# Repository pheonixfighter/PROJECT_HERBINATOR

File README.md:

<!--
  GitHub project README for Project Herbinator.
  Drop this in the repo root as README.md.
-->

<div align="center">

# Project Herbinator 🌱

### Landon Wardle, Robert Cromer, Jasmine Sellers, Juan Ramirez, Zach Worcester, Hunter Mass
### May, 2026

A low-cost smart watering device that keeps small plants alive on its own.
An ESP32-S3 runs a finite-state machine that samples soil moisture, factors in
temperature and humidity, and pumps water only when the plant actually needs it.
A companion Python app monitors the device over Wi-Fi.

<!-- Badge row — these render as little pills on GitHub -->

</div>

---

## Table of Contents

1. [Overview](#overview)
2. [How It Works](#how-it-works)
3. [Hardware](#hardware)
4. [Pinout](#pinout)
5. [Firmware](#firmware)
6. [Calibration](#calibration)
7. [HTTP API](#http-api)
8. [Python Application](#python-application)
9. [Configuration](#configuration)
10. [State and LED Reference](#state-and-led-reference)
11. [Data Logging](#data-logging)
12. [Known Limitations](#known-limitations)

---

# Overview

Herbinator is an automated irrigation device for small-scale plants such as indoor gardens or
windowsill collections. It continuously monitors soil moisture and waters the plant only when the
soil dries below a calibrated threshold, then stops once the soil is satisfied. The goal is to cut
out manual watering while using water efficiently.

The brain is an **ESP32-S3** running firmware structured as a finite-state machine (FSM). The
board reads a capacitive moisture sensor and a DHT11 temperature/humidity sensor, drives a small
submersible pump, and protects itself with a float switch that prevents the pump from running dry.
All readings and pump events are logged to an SD card, and the device hosts a small HTTP server so
a Python app can monitor it remotely.

> [!NOTE]
> To see the Herbinator Roadmap and Project Specification Template
> see the Documentation folder in the repository.

# How It Works

At a high level, Herbinator spends most of its life idling and sampling the moisture sensor
occasionally. When the soil gets too dry it starts the pump, and once the soil is wet enough (or a
safety limit trips) it stops and goes back to idling.

| Step | What happens |
|:-----|:-------------|
| Idle / monitor | The FSM sits in `WaterLoop`, sampling the moisture sensor at a slow interval to save power. |
| Decide | If moisture drops to or below the *on* threshold, it enters `PumpOn`. The threshold is nudged by the current temperature and humidity (see VPD below). |
| Water | The pump runs until soil moisture rises past the *off* threshold, the reservoir runs dry, or a maximum run-time is reached. |
| Recover | After watering it returns to monitoring. If the pump ran for the full safety limit, it first cools down in `PumpCD`. |
| Protect | If the float switch reports no water, or a sensor stops responding, the FSM jumps to the matching error state and parks the pump. |

> [!NOTE]
> The decision threshold is adjusted using **Vapor Pressure Deficit (VPD)**, which is a measure of how fast
> a plant loses water to the air. Hotter, drier air raises the threshold so the plant is watered a
> little sooner; cool, humid air lowers it so watering is delayed. The base *on* threshold is 25%
> and the *off* threshold is 75%, with VPD shifting the *on* threshold by up to +-10%.

# Hardware

Core components for the v1.0 custom PCB:

| Component | Part | Purpose |
|:----------|:-----|:--------|
| Microcontroller | ESP32-S3-WROOM-1 | Runs the FSM firmware, all I/O, and Wi-Fi for Python App |
| Moisture Sensor | Capacitive soil moisture sensor | Estimates soil moisture |
| Temp/Humidity Sensor | DHT11 (U5) | Measures temperature (°C) and humidity |
| Water Pump | 5 V DC mini submersible pump | Delivers water to the plant |
| Float Switch | Magnetic float switch (J5) | Measures if water is available to pump |
| SD Card Reader | SPI SD card module (J4) | Logs readings and pump events to a `.csv` file |
| State LEDs | Green (D2), Blue (D3), Red (D4) | Visual feedback |
| Calibration Button | SW3 tactile push-button | Triggers the moisture calibration routine |
| 3.3 V regulator | AP2112K-3.3V | Powers the ESP32-S3 and sensor logic |
| 5 V regulator + jack | AMS1117-5.0 + 5.5 mm barrel jack | Powers the pump from a wall adapter |
| USB-C | USB-C receptacle (J1, FUSB302) | Alternate power input and serial programming |

> [!NOTE]
> There is no circuitry to switch from the USB-C Port to the
> barrel jack because the PCB was created to have two
> distinct power rails. Both must be plugged in for
> correct results.

> [!NOTE]
> The PCB is still being assembled. More documentation
> and photos will be available once it is done.

# Pinout

GPIO assignments as defined at the top of `ESPMain.ino`:

| Function | Pin | Function | Pin |
|:---------|:---:|:---------|:---:|
| Pump (servo/ESC signal) | 7 | Green LED | 13 |
| Float switch drive (high) | 0 | Blue LED | 12 |
| Float switch read | 10 | Red LED | 11 |
| Moisture sensor (analog) | 4 | Calibration button | 6 |
| DHT11 data | 5 | SD `SCK` | 3 |
| SD `CS` | 18 | SD `MISO` | 46 |
| SD `MOSI` | 8 | | |

> [!NOTE]
> The pump is driven through the `ESP32Servo` library as an ESC-style PWM signal, **not** a raw
> on/off pin. A write of `0` runs the pump at full speed and `90` stops it completely.

# Firmware

The firmware lives in `main/ESPMain/ESPMain.ino` and is built and flashed with the **Arduino IDE** targeting an **ESP32-S3**.

### Required libraries

Install these through the Arduino Library Manager:

`DHT11` · `ESP32Servo` (provides `ESP32PWM`) · `ArduinoJson`

Remaining libraries are available on the **ESP32-S3** by default.

### Build & flash

1. Install the **ESP32 board package** in the Arduino IDE.
2. Open `main/ESPMain/ESPMain.ino`.
3. Select an **ESP32-S3** board and the correct serial port.
4. Set your Wi-Fi credentials (see [Configuration](#configuration)).
5. Upload, then open the Serial Monitor at **9600 baud** (or change the baud rate specified in the code) to watch state transitions.

> [!WARNING]
> On boot the firmware **blocks until the SD card initializes**. If no card is inserted, the red
> LED stays on and the device prints an SD warning in a loop instead of starting the FSM.

# Calibration

Capacitive moisture sensors read different raw values per unit and per soil type, so Herbinator
calibrates against your specific sensor and soil. Calibration values are saved to a simulated
**EEPROM** on the **ESP32-S3** so they are non-volatile.

To calibrate, **hold the button (SW3) for 2 seconds** from the idle state. Herbinator then uses
the LEDs to guide you:

| Step | LED cue | What to do |
|:-----|:--------|:-----------|
| Start | Red flashes 3s | Calibration mode has begun |
| Dry point | Green flashes | Place the sensor in dry soil / air, then press and hold the button |
| Wet point | Blue flashes | For best results water your plant, then place the sensor in the expected wet soil, then press and hold the button. Partially submerging the sensor in a cup of water is also acceptable. |
| Done | All LEDs blink | Done! Wait for Herbinator to resume the water loop. |

> [!NOTE]
> If the stored calibration is missing or invalid on startup, the device automatically drops into
> the calibration routine rather than watering with bad thresholds.

# HTTP API

After connecting to Wi-Fi the device registers an mDNS name and serves a small HTTP API on **port
80**. With mDNS working it is reachable at `http://herbnet.local/`, or directly by its IP address.

| Method | Endpoint | Returns |
|:------:|:---------|:--------|
| `GET` | `/` | JSON snapshot: `temperature`, `humidity`, `moisture`, `state`, `time` |
| `GET` | `/time` | Current time string (synced over NTP) |
| `GET` | `/temperature` | Last temperature reading |
| `GET` | `/humidity` | Last humidity reading |
| `GET` | `/moisture` | Last moisture percentage |
| `GET` | `/state` | Current FSM state name |
| `POST` | `/water` | Acknowledges a manual-water request |

<details>
<summary><b>Example <code>/</code> response</b></summary>

<br>

```json
{
  "temperature": 67,
  "humidity": 21,
  "moisture": 69,
  "state": "PumpOn",
  "time": "2026-05-28 13:45:27"
}
```

</details>

> [!NOTE]
> The `/water` endpoint currently returns a `watering` status but does not yet trigger the pump —
> the actual watering hook is still a TODO. The `/pause` and `/resume` endpoints are scaffolded in
> the firmware but commented out, so the app's pause/resume buttons have nothing to talk to yet.

# Python Application

The desktop app in `python/herbinator.py` is a **Tkinter** GUI that polls the device and displays
live data. It records each sensor's value plus the device's current state, and pulls the timestamp
from the device (synced over NTP).

### Running it

```bash
pip install requests
python herbinator.py
```

### What it shows

The window displays **Temperature**, **Humidity**, **Moisture**, **State**, and **Last Update**,
plus a scrolling log of every request and response. It refreshes automatically every **30 seconds**.

### Buttons

| Button | Action |
|:-------|:-------|
| Water Plant | Sends `POST /water` |
| Pause | Sends `POST /pause` |
| Pause 1 Minute | Sends `POST /pause` with a 60-second duration |
| Resume | Sends `POST /resume` |

> [!NOTE]
> Set `BASE_URL` at the top of `herbinator.py` to your device's address — either `http://herbnet.local`
> (if mDNS resolves on your network) or the device's IP shown in the Serial Monitor on boot. If the
> device is unreachable, every field shows `Disconnected` and the error appears in the log box.

# Configuration

Most tunable values are constants near the top of `ESPMain.ino`:

| Setting | Constant | Default |
|:--------|:---------|:--------|
| Wi-Fi SSID | `ROUTER_NAME` | `HerbyIOT` |
| Wi-Fi password | `ROUTER_PASSWORD` | `herbinator` |
| mDNS name | `mdnsName` | `herbnet` → `herbnet.local` |
| Timezone offset | `gmtOffset_sec` | `-28800` (PST) |
| Moisture *on* threshold | `ON_THRESHOLD_BASE` | `0.25` |
| Moisture *off* threshold | `OFF_THRESHOLD_BASE` | `0.75` |
| Max pump run-time | `MAX_PUMP_ON_MS` | 45s |
| Long-run pump cooldown | `PUMP_CD_MILLIS` | 5 min |
| Idle sample interval | `WATER_LOOP_SAMPLE_MS` | 5s |
| Calibration hold time | `CALIBRATION_HOLD_MS` | 2s |

> [!WARNING]
> Wi-Fi credentials are stored in plain text in the source. Don't commit real network credentials
> to a public repository.

# State and LED Reference

The FSM has the following states. The three status LEDs signal what the device is doing at a glance:

| State | Meaning | LEDs |
|:------|:--------|:-----|
| `MainLoop` | Validates calibration, checks for water, then enters monitoring | Green |
| `WaterLoop` | Idle monitoring; sampling soil moisture | Green |
| `PumpOn` | Pump running | Blue |
| `PumpOff` | Pump shutting off | Off |
| `PumpCD` | Cooldown after a long pump run | Red (flashing) |
| `NoWater` | Reservoir empty (float switch) — pump parked | Red + Blue |
| `RedFlash` | Entry into calibration | Red (flashing) |
| `PromptDry` | Waiting for dry calibration point | Green (flashing) |
| `PromptWet` | Waiting for wet calibration point | Blue (flashing) |
| `ButtonPressed` / `CalibrationButtonYield` | Hold-detection during calibration | N/A |
| `CalibrationDone` | Calibration saved | All (blinking) |
| `MoistureSensorFail` | Moisture sensor out of range / unresponsive | Red (fast flash) + Blue |
| `TempSensorFail` | DHT11 unresponsive | Red (fast flash) + Green |

# Data Logging

When an SD card is present, the firmware appends every sensor cycle and pump event to
`/herbinator_logs.txt` as CSV, flushing to the card every 30 seconds. Columns:

```text
timestamp_ms, state, rawMoist, moist_pct, on_thresh, temp_c,
humidity_pct, vpd_kpa, dht_ok, pump_on, water_raw, water_present
```

This makes it easy to pull the card afterward and analyze how the soil dried and recovered around
each watering event. It is recommended to do this in MATLAB or similar software that can crunch 
large .csv files quickly.

# Known Limitations

- **Manual watering isn't wired up.** `/water` returns a status but doesn't actually run the pump yet.
- **Pause/resume are stubs.** Those firmware endpoints are commented out, so the app's Pause / Resume / Pause 1 Minute buttons have no effect on the device.
- **CLI is a placeholder.** `python/interface.py` is an early scaffold and not yet a working interface.
- **Credentials are hardcoded.** Wi-Fi SSID/password live in the firmware source.

<!--
  Suggested next steps for the team:
  - Implement the watering hook behind /water and reinstate /pause + /resume to match the app.
  - Move Wi-Fi credentials out of source (e.g. a config the user enters, or a secrets header that's gitignored).
  - Finish interface.py or remove it if the Tkinter app is the path forward.
  - Consider documenting the BOM footprint lessons from the spec doc here too.
-->

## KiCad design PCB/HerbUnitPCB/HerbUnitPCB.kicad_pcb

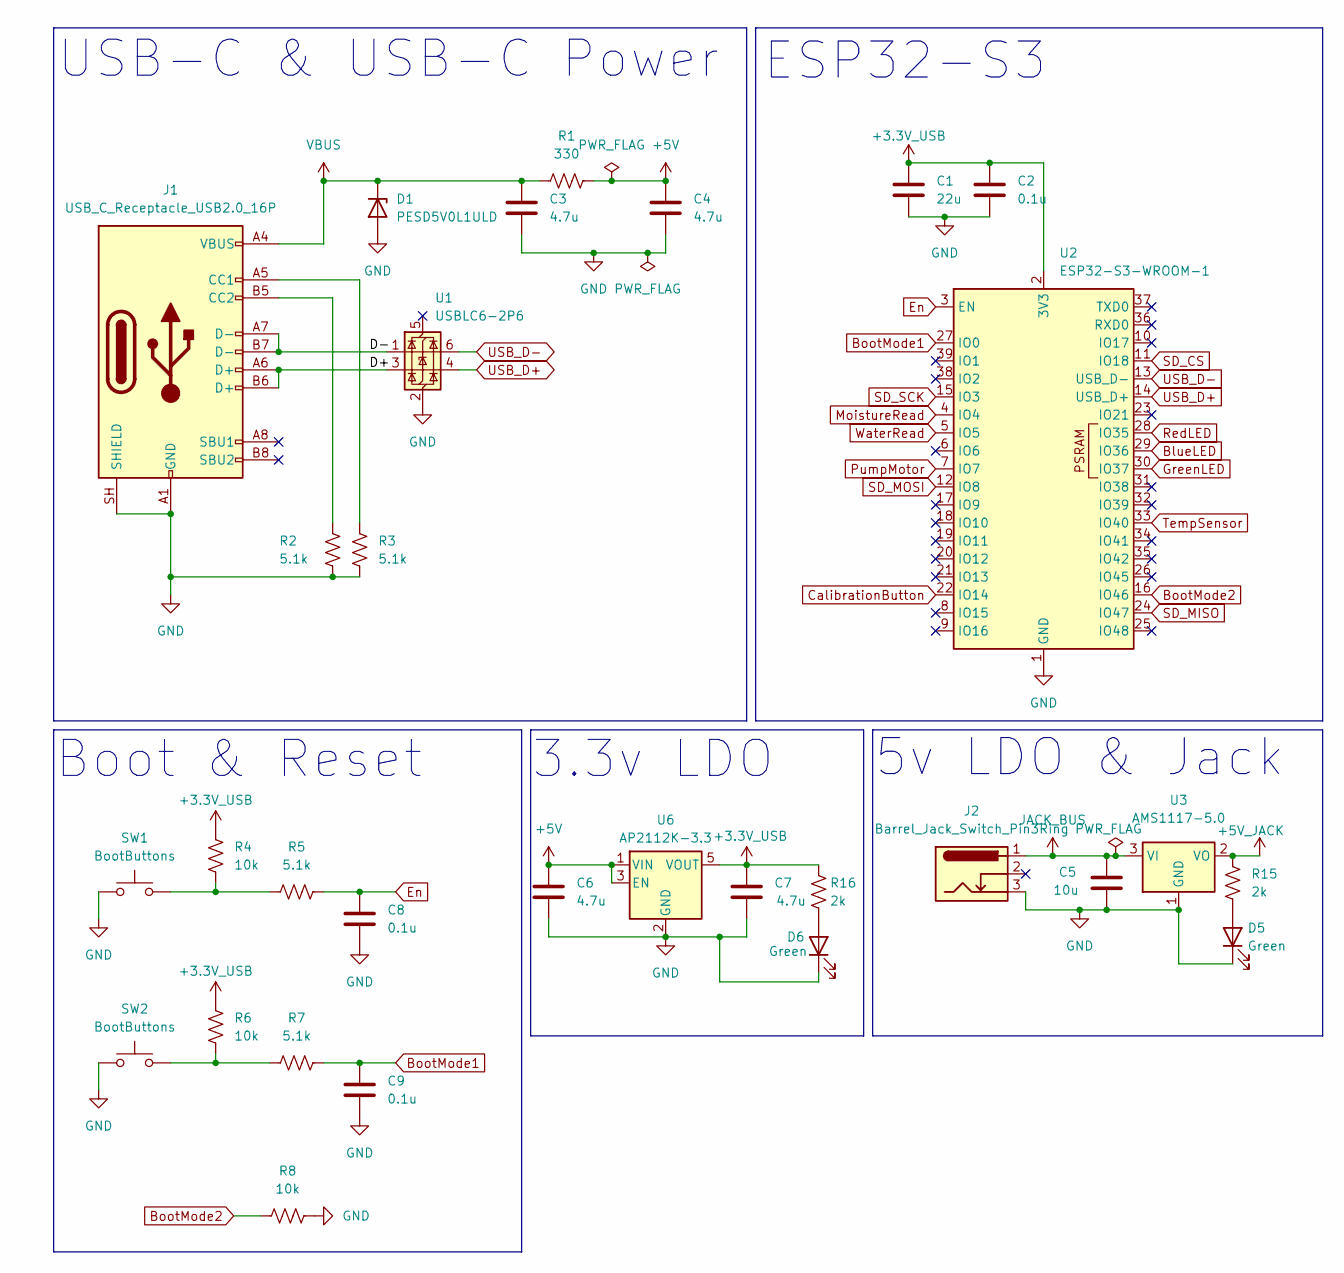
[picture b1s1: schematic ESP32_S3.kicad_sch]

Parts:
C1: 22u; C_0805_2012Metric; MPN GRM21BR61E226ME44K
C2, C8, C9: 0.1u; C_0402_1005Metric; MPN GRM155R62A104KE14D
C3, C4, C6, C7: 4.7u; C_0402_1005Metric; MPN GRM155R61A475MEAAD
C5: 10u; C_1206_3216Metric; MPN GRM319R61E106KA12D
D1: PESD5V0L1ULD; D_SOD-882D; MPN SOD882
D5, D6: Green; LED_APT2012CGCK
J1: USB_C_Receptacle_USB2.0_16P; USB_C_Receptacle_G-Switch_GT-USB-7010ASV; MPN UJ31-CH-3-SMT-TR
J2: Barrel_Jack_Switch_Pin3Ring; BarrelJack_Horizontal; MPN PJ-002A
R1: 330; R_0805_2012Metric; MPN RC0805FR-10330RL
R2, R3, R5, R7: 5.1k; R_0402_1005Metric; MPN RT0402DRE075K1L
R4, R6, R8: 10k; R_0402_1005Metric; MPN RC0402FR-1310KL
R15, R16: 2k; R_0402_1005Metric; MPN AC0402FR-072KL
SW1, SW2: BootButtons; SW_SPST_B3U-1000P; MPN B3U-1000P
U1: USBLC6-2P6; SOT-666; MPN USBLC6-2P6
U2: ESP32-S3-WROOM-1; MPN ESP32-S3-WROOM-1-N8
U3: AMS1117-5.0; SOT-223-3_TabPin2; MPN AMS1117-5.0(XBLW)
U6: AP2112K-3.3; SOT-23-5; MPN AP2112K-3.3TRG1

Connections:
+3.3V_USB: C1.1, C2.1, C7.1, R4.1, R6.1, R16.1, U2.2 (3V3), U6.5 (VOUT); also elsewhere on the board
+5V: C4.1, C6.1, R1.2, U6.1 (VIN), U6.3 (EN)
+5V_JACK: R15.1, U3.2 (VO); also elsewhere on the board
/ESP32-S3/D+: J1.A6 (D+), J1.B6 (D+), U1.3 (I/O2)
/ESP32-S3/D-: J1.A7 (D-), J1.B7 (D-), U1.1 (I/O1)
BlueLED: U2.29 (IO36); also elsewhere on the board
BootMode1: C9.1, R7.2, U2.27 (IO0)
BootMode2: R8.1, U2.16 (IO46)
CalibrationButton: U2.22 (IO14); also elsewhere on the board
En: C8.1, R5.2, U2.3 (EN)
GND: C1.2, C2.2, C3.2, C4.2, C5.2, C6.2, C7.2, C8.2, C9.2, D1.2 (A), D5.1 (K), D6.1 (K), J1.A1 (GND), J1.A12 (GND), J1.B1 (GND), J1.B12 (GND), J1.SH (SHIELD), J2.3, R2.1, R3.2, R8.2, SW1.1, SW2.1, U1.2 (GND), U2.1 (GND), U2.40 (GND), U2.41 (GND), U3.1 (GND), U6.2 (GND); also elsewhere on the board
GreenLED: U2.30 (IO37); also elsewhere on the board
JACK_BUS: C5.1, J2.1, U3.3 (VI)
MoistureRead: U2.4 (IO4); also elsewhere on the board
unnamed: D5.2 (A), R15.2
unnamed: D6.2 (A), R16.2
unnamed: J1.A5 (CC1), R3.1
unnamed: J1.B5 (CC2), R2.2
unnamed: R4.2, R5.1, SW1.2
unnamed: R6.2, R7.1, SW2.2
PumpMotor: U2.7 (IO7); also elsewhere on the board
RedLED: U2.28 (IO35); also elsewhere on the board
SD_CS: U2.11 (IO18); also elsewhere on the board
SD_MISO: U2.24 (IO47); also elsewhere on the board
SD_MOSI: U2.12 (IO8); also elsewhere on the board
SD_SCK: U2.15 (IO3); also elsewhere on the board
TempSensor: U2.33 (IO40); also elsewhere on the board
USB_D+: U1.4 (I/O2), U2.14 (USB_D+)
USB_D-: U1.6 (I/O1), U2.13 (USB_D-)
VBUS: C3.1, D1.1 (K), J1.A4 (VBUS), J1.A9 (VBUS), J1.B4 (VBUS), J1.B9 (VBUS), R1.1
WaterRead: U2.5 (IO5); also elsewhere on the board

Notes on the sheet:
ESP32-S3
5v LDO & Jack
3.3v LDO
Boot & Reset
USB-C & USB-C Power

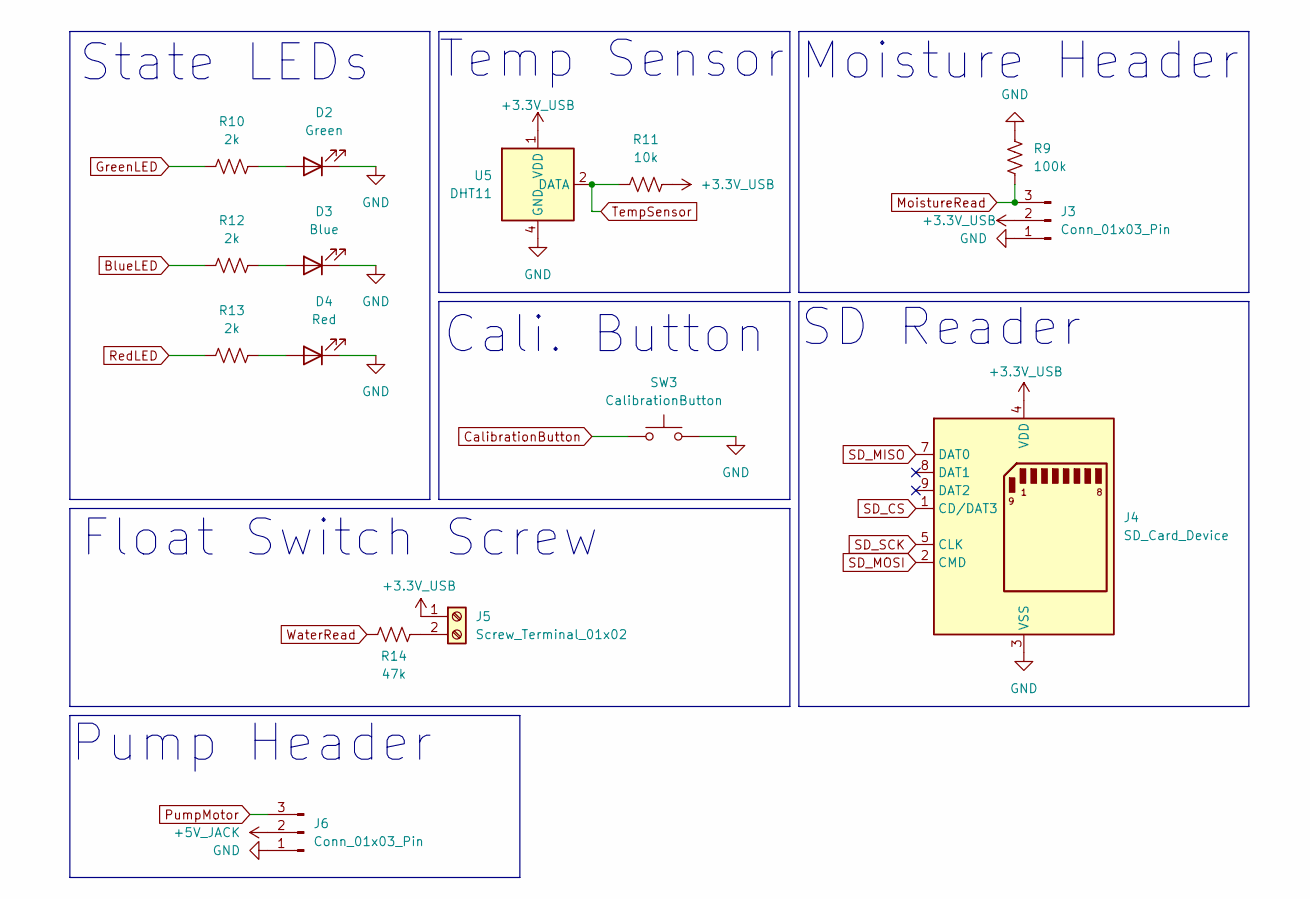
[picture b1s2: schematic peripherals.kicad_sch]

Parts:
D2: Green; LED_APT2012CGCK; MPN APT2012CGCK
D3: Blue; LED_APT2012VBC_D; MPN APT2012VBC_D
D4: Red; LED_APT2012EC; MPN APT2012EC
J3, J6: Conn_01x03_Pin; PinHeader_1x03_P2.54mm_Horizontal; MPN 61300311021
J4: SD_Card_Device; SD_Hirose_DM1AA_SF_PEJ82; MPN MSD-3-A
J5: Screw_Terminal_01x02; TerminalBlock_Phoenix_MKDS-1,5-2-5.08_1x02_P5.08mm_Horizont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; MPN 1715721
R9: 100k; R_0805_2012Metric; MPN RC0805JR-07100KL
R10, R12, R13: 2k; R_0402_1005Metric; MPN AC0402FR-072KL
R11: 10k; R_0402_1005Metric; MPN RC0402FR-1310KL
R14: 47k; R_0805_2012Metric; MPN RT0805FRE0747KL
SW3: CalibrationButton; SW_Push_1P1T_NO_CK_PTS125Sx43SMTR; MPN PTS125SM43
U5: DHT11; Aosong_DHT11_5.5x12.0_P2.54mm; MPN DHT11

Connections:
+3.3V_USB: J3.2, J4.4 (VDD), J5.1, R11.2, U5.1 (VDD); also elsewhere on the board
+5V_JACK: J6.2; also elsewhere on the board
BlueLED: R12.1; also elsewhere on the board
CalibrationButton: SW3.1; also elsewhere on the board
GND: D2.1 (K), D3.1 (K), D4.1 (K), J3.1, J4.3 (VSS), J4.6 (VSS), J6.1, R9.2, SW3.2, U5.4 (GND); also elsewhere on the board
GreenLED: R10.1; also elsewhere on the board
MoistureRead: J3.3, R9.1; also elsewhere on the board
unnamed: D2.2 (A), R10.2
unnamed: D3.2 (A), R12.2
unnamed: D4.2 (A), R13.2
unnamed: J5.2, R14.2
PumpMotor: J6.3; also elsewhere on the board
RedLED: R13.1; also elsewhere on the board
SD_CS: J4.1 (CD/DAT3); also elsewhere on the board
SD_MISO: J4.7 (DAT0); also elsewhere on the board
SD_MOSI: J4.2 (CMD); also elsewhere on the board
SD_SCK: J4.5 (CLK); also elsewhere on the board
TempSensor: R11.1, U5.2 (DATA); also elsewhere on the board
WaterRead: R14.1; also elsewhere on the board

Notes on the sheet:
Float Switch Screw
Cali. Button
State LEDs
Moisture Header
Pump Header
Temp Sensor
SD Reader

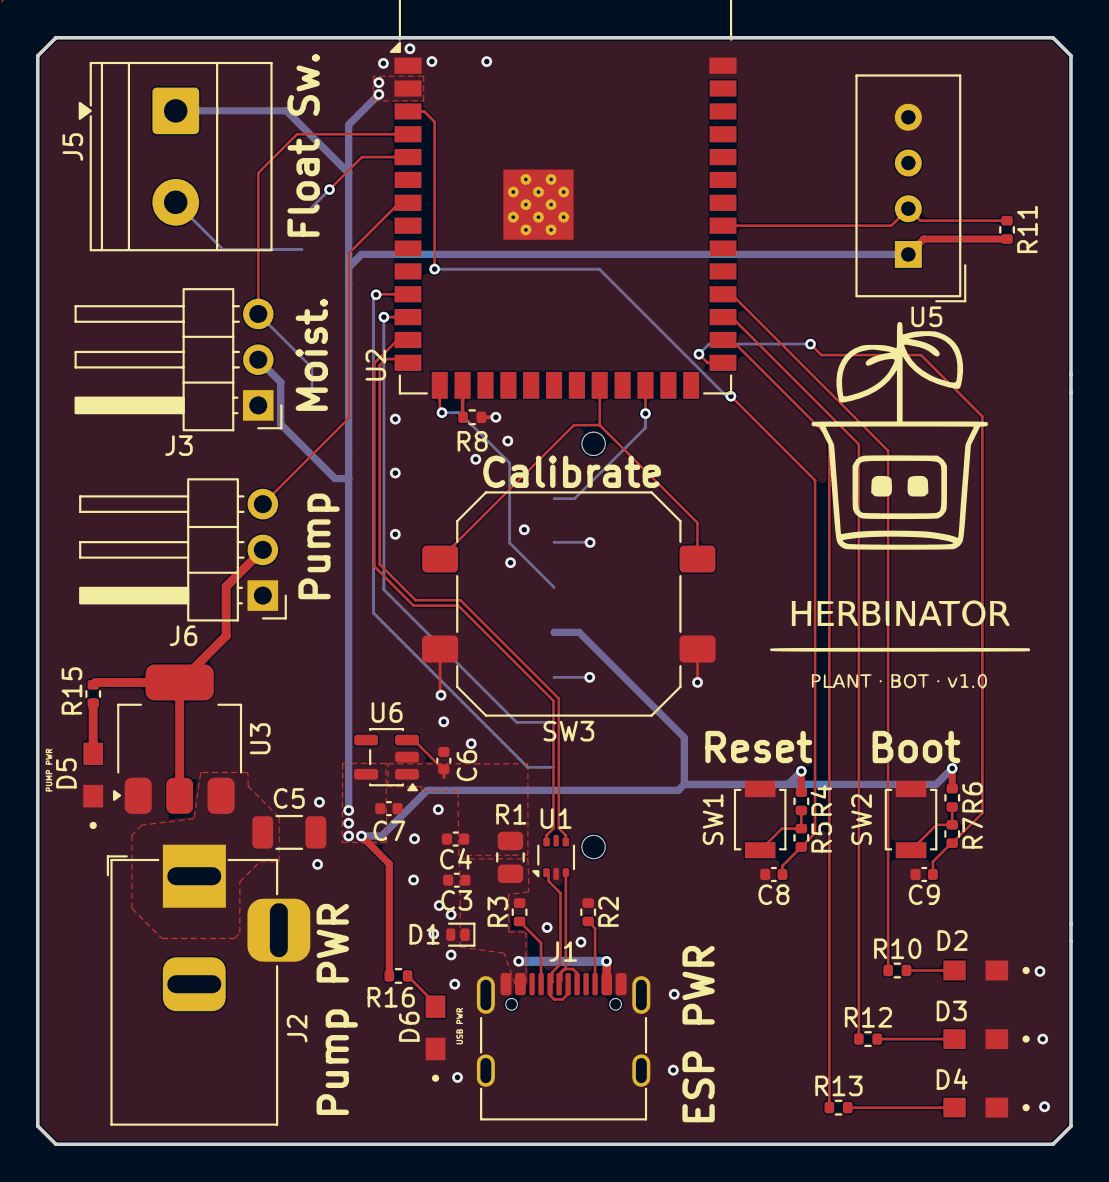
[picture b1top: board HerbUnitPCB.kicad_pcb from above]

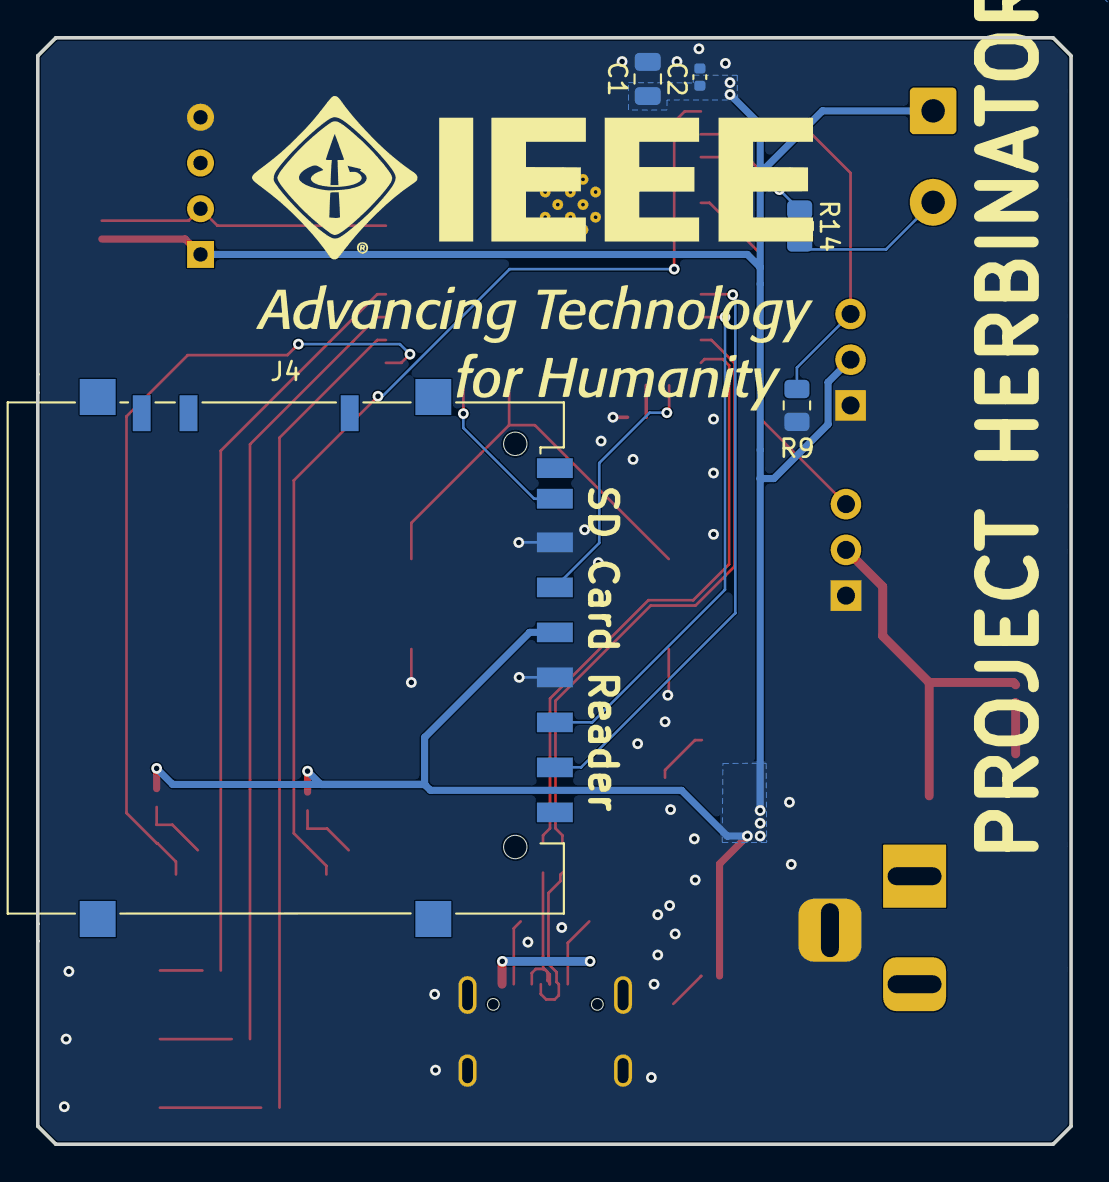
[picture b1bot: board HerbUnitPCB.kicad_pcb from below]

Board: 2 copper layers, 57.4 x 61.5 mm, 45 parts (5 on the bottom side), 35 nets.

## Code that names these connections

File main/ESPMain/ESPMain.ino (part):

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const int BLUE_LED = 12;
const int RED_LED = 11;
const int BUTTON = 6;
const int SD_CS = 18;
const int SD_MOSI = 8;
const int SD_SCK = 3; // Clk
const int SD_MISO = 46;

/* The baud rate to the serial monitor. */
const unsigned int BAUD_RATE = 9600;
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
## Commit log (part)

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2026-04-17 Added some python outline
2026-05-06 Basecode
2026-05-09 Need to figure out JSON
2026-05-12 PCB files added back
2026-05-14 Started PCB
2026-05-15 Lock files
2026-05-16 added a function to update the herbinator information sent via HTTP
2026-05-23 Finished arrangement, fixed silkscreen
2026-05-23 Lock file
2026-05-25 PCB Routed + Silkscreen
2026-05-25 Started fabrication files
2026-05-26 network code integrated
2026-05-27 New Gerber
2026-05-28 Updated BOM to have all parts.
2026-06-19 Documentation for IEEE
2026-06-19 Update calibration button yield status to N/A
